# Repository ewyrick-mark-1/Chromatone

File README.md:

# Chromatone

**Author:** Elliot Wyrick

## Overview

Chromatone is an embedded audio visualizer running on the Raspberry Pi RP2350. It samples audio through the ADC, performs a real-time FFT, detects musical notes, and drives an RGB LED output based on the results.

## [Demo video:](https://youtu.be/pOVmz1aZbJg)

## Hardware

- **MCU:** Raspberry Pi RP2350 (overclocked to 300 MHz)
- **Input:** Analog microphone on ADC channel 0 (GPIO 40)
- **Output:** RGB LED via PWM on GPIO 37–39
- **Schematics/PCB:** KiCad project files located in `KiCad/`

## How It Works

Audio is captured at 20 kHz using DMA ping-pong buffers. Each buffer triggers a 16384 point FFT with 50% overlap and a Hanning window applied. Detected frequency peaks are mapped to MIDI notes (A0–C8), and the corresponding hue is output to the RGB LED.

Two display modes are available (toggled via `display_mode` in `main.c`):
- **Mode 0:** Logarithmic frequency spectrum
- **Mode 1:** Musical note detection

## Color Math

Each of the 12 chromatic notes is assigned a fixed hue evenly spaced around the color wheel (360° / 12 = 30° per note), with C at 0° (red) through B at 330° (pink).

Detected peaks are converted to a note index using the standard MIDI formula:

```
n = 12 × log₂(f / 440) + 69
```

When multiple notes are detected simultaneously, their hues are blended using a **circular weighted average**- each hue is converted to a unit vector on the color wheel, weighted by FFT magnitude, and the vectors are summed:

```
x = Σ( cos(hue_i) × weight_i )
y = Σ( sin(hue_i) × weight_i )
blended_hue = atan2(y, x)
```

This handles wraparound correctly (e.g. blending 10° and 350° yields 0°, not 180°).

The blended hue is then smoothed over time using an exponential moving average on the shortest angular path (15% per frame) to avoid jarring color jumps between notes.

Finally, the smoothed hue is converted from HSV (full saturation and brightness) to RGB via the standard piecewise HSV→RGB formula and output as an 8-bit PWM duty cycle on each channel.

## Build & Flash

This project uses [PlatformIO](https://platformio.org/) with the Proton board target.

```
pio run
pio run --target upload
```

Serial monitor at 115200 baud:
```
pio device monitor
```

Alternativly, and what I used during development, the platform IO extension works well. It provides gui upload and monitor buttons.

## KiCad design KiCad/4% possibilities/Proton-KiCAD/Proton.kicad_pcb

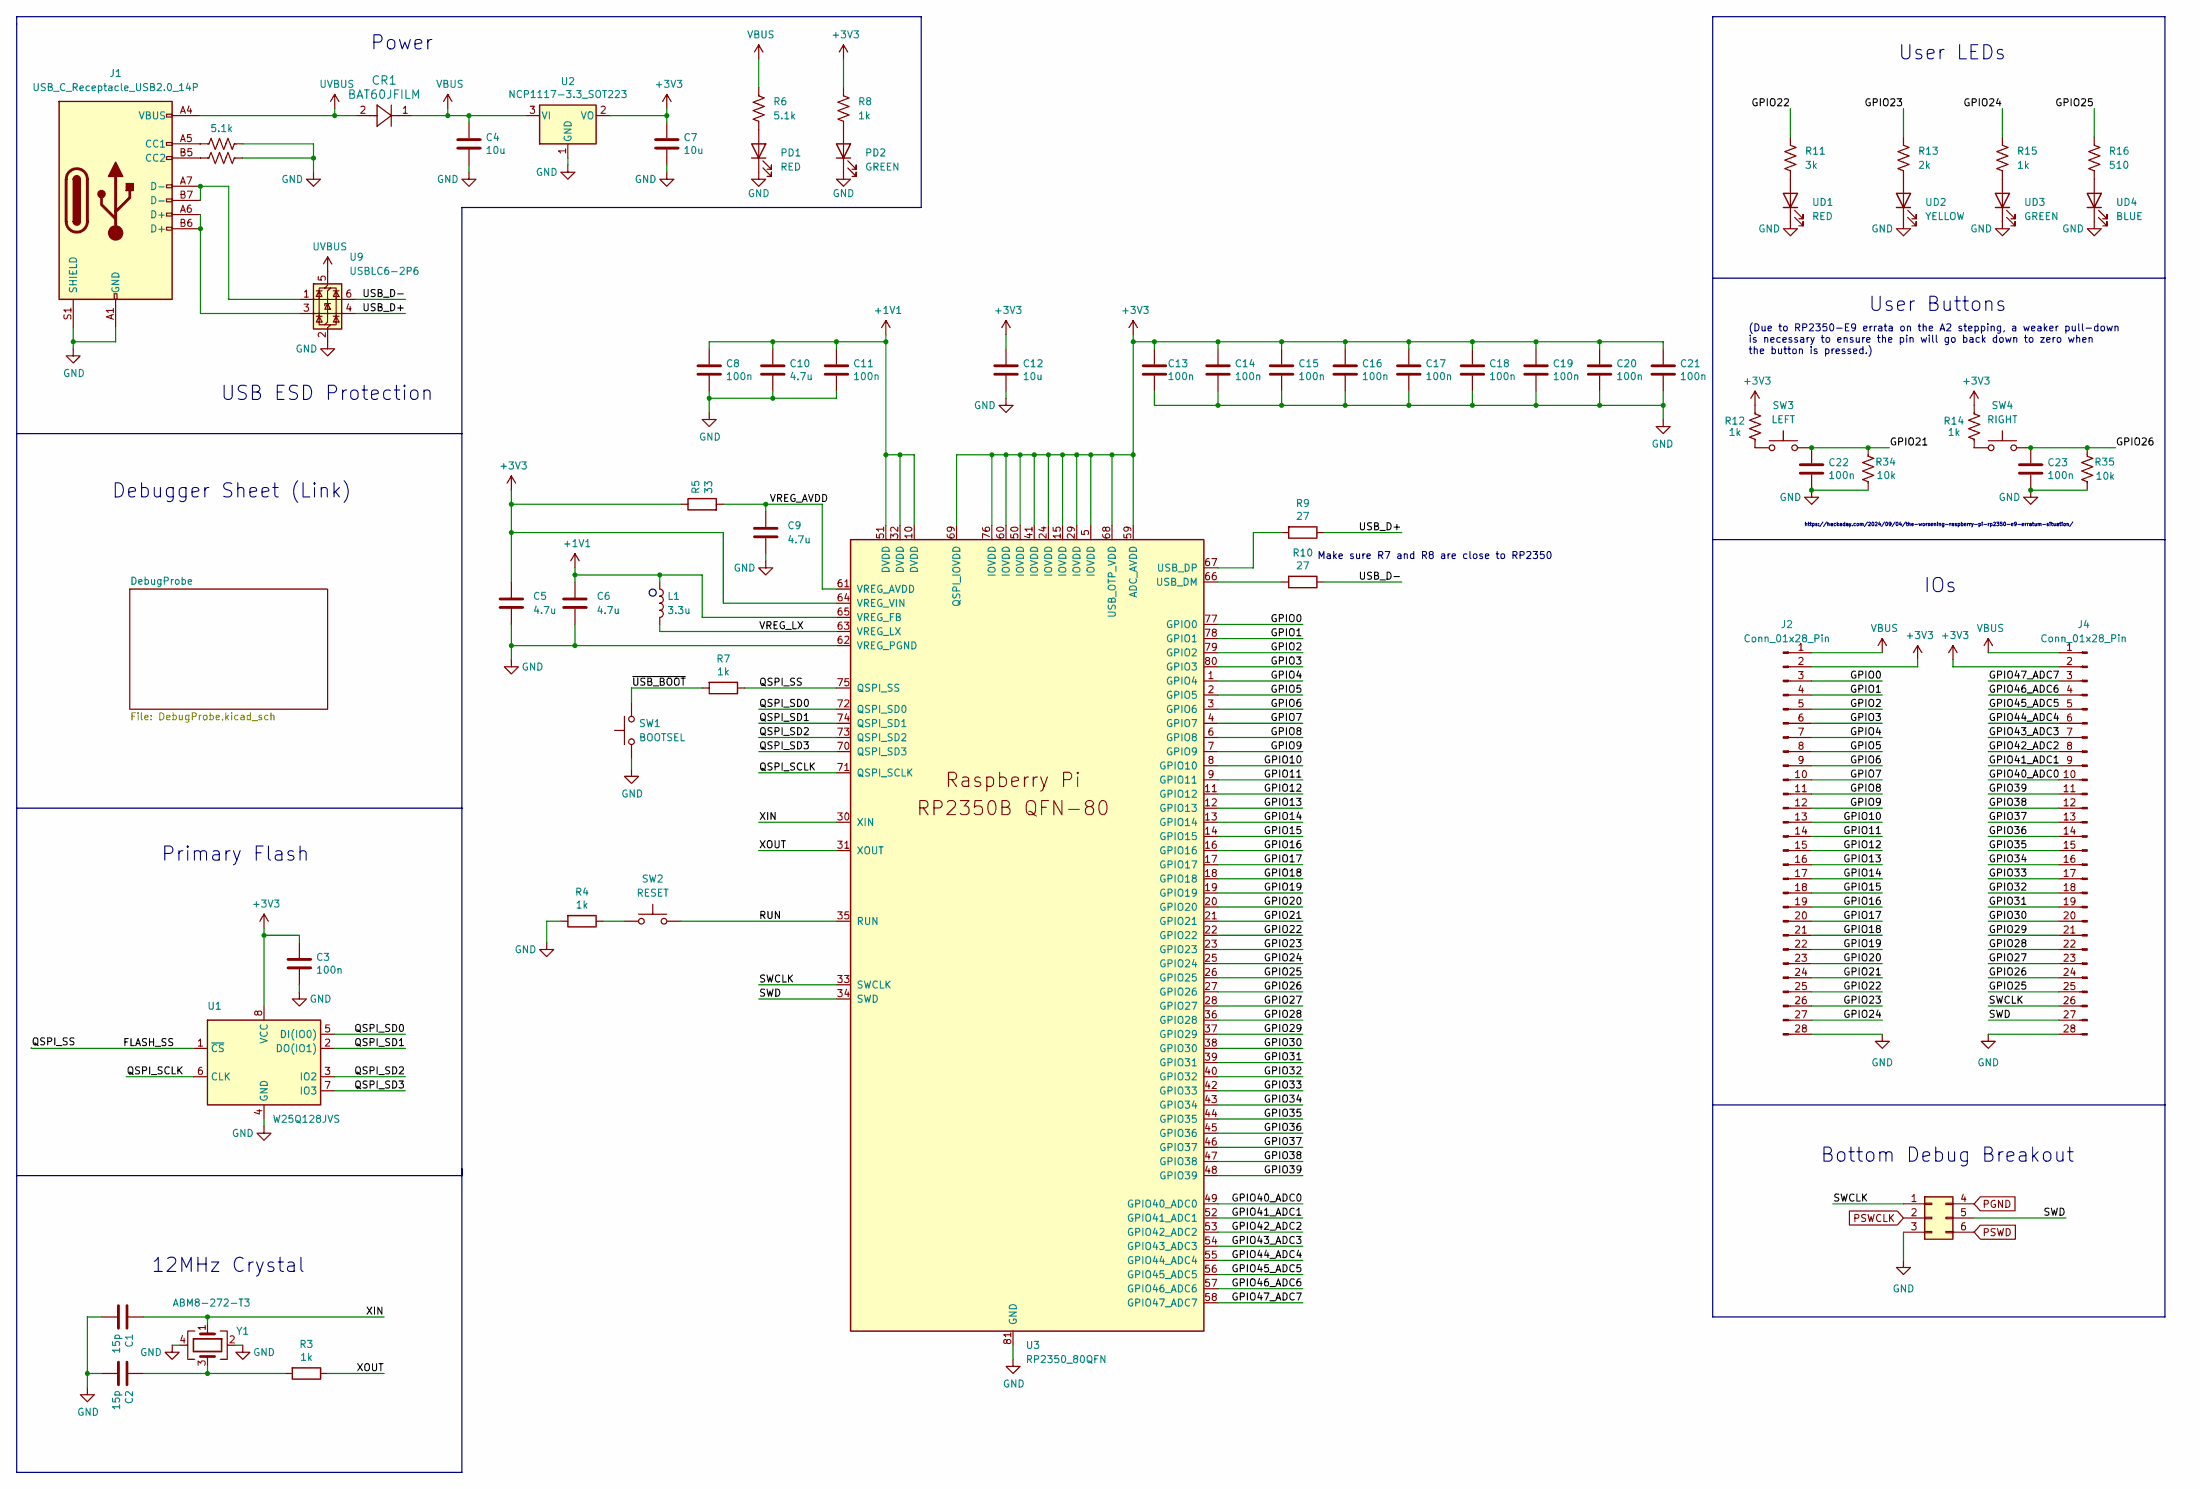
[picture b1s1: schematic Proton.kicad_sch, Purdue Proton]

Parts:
C1, C2: 15p; C_0402_1005Metric
C3, C8, C11, C13, C14, C15, C16, C17, C18, C19, C20, C21, C22, C23: 100n; C_0402_1005Metric
C4, C7, C12: 10u; C_0805_2012Metric
C5, C6: 4.7u; C_0402_1005Metric_small_pads
C9, C10: 4.7u; C_0402_1005Metric
CR1: BAT60JFILM; CR_60JFILM_STM
J1: USB_C_Receptacle_USB2.0_14P; USB_C_Receptacle_G-Switch_GT-USB-7010ASV
J2, J4: Conn_01x28_Pin; PinHeader_1x28_P2.54mm_Vertical
J6: Conn_02x03_Top_Bottom; PinSocket_2x03_P2.54mm_Vertical
L1: 3.3u; L_pol_2016
PD1: RED; LED_0805_2012Metric
PD2: GREEN; LED_0805_2012Metric
R1, R2, R6: 5.1k; R_0402_1005Metric
R3, R4, R7, R8, R12, R14, R15: 1k; R_0402_1005Metric
R5: 33; R_0402_1005Metric
R9, R10: 27; R_0402_1005Metric
R11: 3k; R_0402_1005Metric
R13: 2k; R_0402_1005Metric
R16: 510; R_0402_1005Metric
R34, R35: 10k; R_0402_1005Metric
SW1: BOOTSEL; SW_SPST_PTS647_Sx38
SW2: RESET; SW_SPST_PTS647_Sx38
SW3: LEFT; SW_SPST_PTS647_Sx38
SW4: RIGHT; SW_SPST_PTS647_Sx38
U1: W25Q128JVS; SOIC-8_5.23x5.23mm_P1.27mm
U2: NCP1117-3.3_SOT223; SOT-223-3_TabPin2
U3: RP2350_80QFN; RP2350-QFN-80-1EP_10x10_P0.4mm_EP3.4x3.4mm_ThermalVias
U9: USBLC6-2P6; SOT-666
UD1: RED; LED_0805_2012Metric
UD2: YELLOW; LED_0805_2012Metric
UD3: GREEN; LED_0805_2012Metric
UD4: BLUE; LED_0805_2012Metric
Y1: ABM8-272-T3; Crystal_SMD_3225-4Pin_3.2x2.5mm

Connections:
+1V1: C6.1, C8.1, C10.1, C11.1, L1.1, U3.10 (DVDD), U3.32 (DVDD), U3.51 (DVDD), U3.65 (VREG_FB)
+3V3: C3.1, C5.1, C7.1, C12.1, C13.1, C14.1, C15.1, C16.1, C17.1, C18.1, C19.1, C20.1, C21.1, J2.2, J4.2, R5.1, R8.1, R12.1, R14.1, U1.8 (VCC), U2.2 (VO), U3.5 (IOVDD), U3.15 (IOVDD), U3.24 (IOVDD), U3.29 (IOVDD), U3.41 (IOVDD), U3.50 (IOVDD), U3.59 (ADC_AVDD), U3.60 (IOVDD), U3.64 (VREG_VIN), U3.68 (USB_OTP_VDD), U3.69 (QSPI_IOVDD), U3.76 (IOVDD)
/FLASH_SS: R7.1, U1.1 (~CS), U3.75 (QSPI_SS)
/GPIO0: J2.3, U3.77 (GPIO0)
/GPIO1: J2.4, U3.78 (GPIO1)
/GPIO2: J2.5, U3.79 (GPIO2)
/GPIO3: J2.6, U3.80 (GPIO3)
/GPIO4: J2.7, U3.1 (GPIO4)
/GPIO5: J2.8, U3.2 (GPIO5)
/GPIO6: J2.9, U3.3 (GPIO6)
/GPIO7: J2.10, U3.4 (GPIO7)
/GPIO8: J2.11, U3.6 (GPIO8)
/GPIO9: J2.12, U3.7 (GPIO9)
/GPIO10: J2.13, U3.8 (GPIO10)
/GPIO11: J2.14, U3.9 (GPIO11)
/GPIO12: J2.15, U3.11 (GPIO12)
/GPIO13: J2.16, U3.12 (GPIO13)
/GPIO14: J2.17, U3.13 (GPIO14)
/GPIO15: J2.18, U3.14 (GPIO15)
/GPIO16: J2.19, U3.16 (GPIO16)
/GPIO17: J2.20, U3.17 (GPIO17)
/GPIO18: J2.21, U3.18 (GPIO18)
/GPIO19: J2.22, U3.19 (GPIO19)
/GPIO20: J2.23, U3.20 (GPIO20)
/GPIO21: C22.1, J2.24, R34.2, SW3.2, U3.21 (GPIO21)
/GPIO22: J2.25, R11.1, U3.22 (GPIO22)
/GPIO23: J2.26, R13.1, U3.23 (GPIO23)
/GPIO24: J2.27, R15.1, U3.25 (GPIO24)
/GPIO25: J4.25, R16.1, U3.26 (GPIO25)
/GPIO26: C23.1, J4.24, R35.2, SW4.2, U3.27 (GPIO26)
/GPIO27: J4.23, U3.28 (GPIO27)
/GPIO28: J4.22, U3.36 (GPIO28)
/GPIO29: J4.21, U3.37 (GPIO29)
/GPIO30: J4.20, U3.38 (GPIO30)
/GPIO31: J4.19, U3.39 (GPIO31)
/GPIO32: J4.18, U3.40 (GPIO32)
/GPIO33: J4.17, U3.42 (GPIO33)
/GPIO34: J4.16, U3.43 (GPIO34)
/GPIO35: J4.15, U3.44 (GPIO35)
/GPIO36: J4.14, U3.45 (GPIO36)
/GPIO37: J4.13, U3.46 (GPIO37)
/GPIO38: J4.12, U3.47 (GPIO38)
/GPIO39: J4.11, U3.48 (GPIO39)
/GPIO40_ADC0: J4.10, U3.49 (GPIO40_ADC0)
/GPIO41_ADC1: J4.9, U3.52 (GPIO41_ADC1)
/GPIO42_ADC2: J4.8, U3.53 (GPIO42_ADC2)
/GPIO43_ADC3: J4.7, U3.54 (GPIO43_ADC3)
/GPIO44_ADC4: J4.6, U3.55 (GPIO44_ADC4)
/GPIO45_ADC5: J4.5, U3.56 (GPIO45_ADC5)
/GPIO46_ADC6: J4.4, U3.57 (GPIO46_ADC6)
/GPIO47_ADC7: J4.3, U3.58 (GPIO47_ADC7)
/QSPI_SCLK: U1.6 (CLK), U3.71 (QSPI_SCLK)
/QSPI_SD0: U1.5 (DI(IO0)), U3.72 (QSPI_SD0)
/QSPI_SD1: U1.2 (DO(IO1)), U3.74 (QSPI_SD1)
/QSPI_SD2: U1.3 (IO2), U3.73 (QSPI_SD2)
/QSPI_SD3: U1.7 (IO3), U3.70 (QSPI_SD3)
/RUN: SW2.2, U3.35 (RUN)
/SWCLK: J4.26, J6.1, U3.33 (SWCLK)
/SWD: J4.27, J6.5, U3.34 (SWD)
/USB_D+: R9.1, U9.4 (I/O2)
/USB_D-: R10.1, U9.6 (I/O1)
/VREG_AVDD: C9.1, R5.2, U3.61 (VREG_AVDD)
/VREG_LX: L1.2, U3.63 (VREG_LX)
/XIN: C1.1, U3.30 (XIN), Y1.1
/XOUT: R3.1, U3.31 (XOUT)
/~USB_BOOT: R7.2, SW1.2
GND: C1.2, C2.2, C3.2, C4.2, C5.2, C6.2, C7.2, C8.2, C9.2, C10.2, C11.2, C12.2, C13.2, C14.2, C15.2, C16.2, C17.2, C18.2, C19.2, C20.2, C21.2, C22.2, C23.2, J1.A1 (GND), J1.A12 (GND), J1.B1 (GND), J1.B12 (GND), J1.S1 (SHIELD), J2.28, J4.28, J6.3, PD1.1 (K), PD2.1 (K), R1.2, R2.2, R4.2, R34.1, R35.1, SW1.1, U1.4 (GND), U2.1 (GND), U3.62 (VREG_PGND), U3.81 (GND), U9.2 (GND), UD1.1 (K), UD2.1 (K), UD3.1 (K), UD4.1 (K), Y1.2, Y1.4
unnamed: C2.1, R3.2, Y1.3
unnamed: J1.A5 (CC1), R1.1
unnamed: J1.B5 (CC2), R2.1
unnamed: J1.A6 (D+), J1.B6 (D+), U9.3 (I/O2)
unnamed: J1.A7 (D-), J1.B7 (D-), U9.1 (I/O1)
unnamed: PD1.2 (A), R6.2
unnamed: PD2.2 (A), R8.2
unnamed: R4.1, SW2.1
unnamed: R12.2, SW3.1
unnamed: R14.2, SW4.1
unnamed: R10.2, U3.66 (USB_DM)
unnamed: R9.2, U3.67 (USB_DP)
unnamed: R11.2, UD1.2 (A)
unnamed: R13.2, UD2.2 (A)
unnamed: R15.2, UD3.2 (A)
unnamed: R16.2, UD4.2 (A)
PGND: J6.4; also elsewhere on the board
PSWCLK: J6.2; also elsewhere on the board
PSWD: J6.6; also elsewhere on the board
UVBUS: CR1.2, J1.A4 (VBUS), J1.A9 (VBUS), J1.B4 (VBUS), J1.B9 (VBUS), U9.5 (VBUS)
VBUS: C4.1, CR1.1, J2.1, J4.1, R6.1, U2.3 (VI)

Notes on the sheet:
https://hackaday.com/2024/09/04/the-worsening-raspberry-pi-rp2350-e9-erratum-situation/
IOs
12MHz Crystal
Bottom Debug Breakout
Primary Flash
User LEDs
Make sure R7 and R8 are close to RP2350
Debugger Sheet (Link)
USB ESD Protection
User Buttons
Power
(Due to RP2350-E9 errata on the A2 stepping, a weaker pull-down is necessary to ensure the pin will go back down to zero when the button is pressed.)

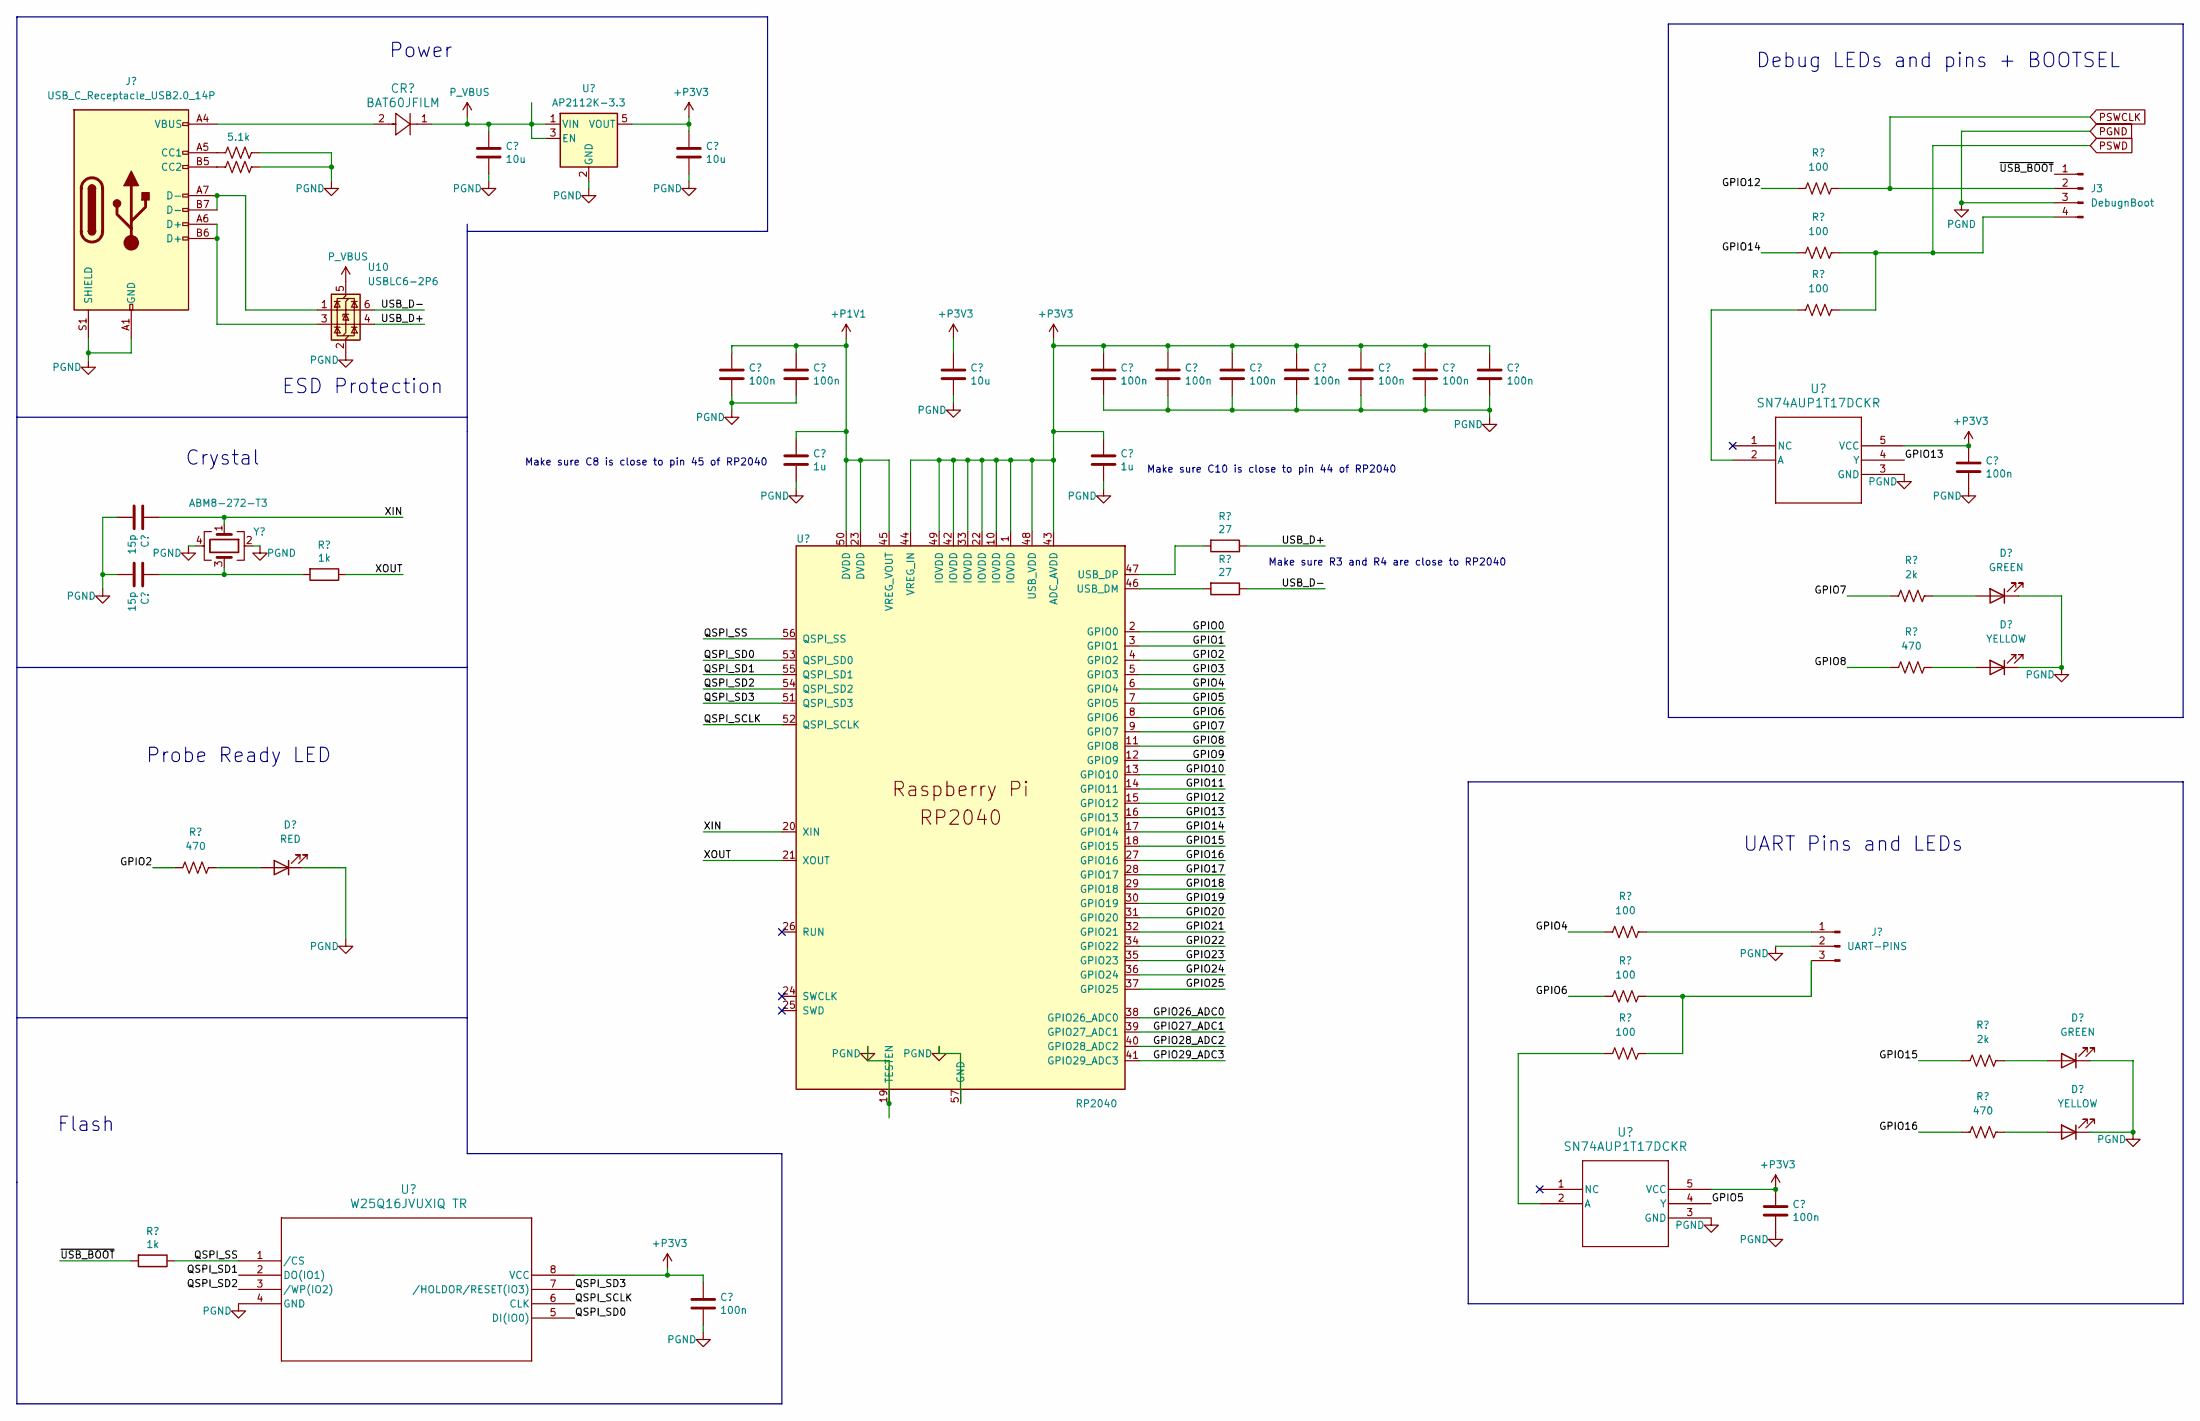
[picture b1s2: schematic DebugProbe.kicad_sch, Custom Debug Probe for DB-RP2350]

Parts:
C24, C25: 15p; C_0402_1005Metric
C26: 10u; C_0805_2012Metric
C27, C32: 10u; C_0603_1608Metric
C28, C29, C30, C33, C35, C36, C37, C38, C39, C40, C41, C42: 100n; C_0402_1005Metric
C31, C34: 1u; C_0402_1005Metric
CR2: BAT60JFILM; CR_60JFILM_STM
D1: RED; D_0402_1005Metric
D2, D4: GREEN; D_0402_1005Metric
D3, D5: YELLOW; D_0402_1005Metric
J3: DebugnBoot; PinHeader_1x04_P2.54mm_Vertical
J5: USB_C_Receptacle_USB2.0_14P; USB_C_Receptacle_G-Switch_GT-USB-7010ASV
J7: UART-PINS; PinHeader_1x03_P2.54mm_Vertical
R17, R20: 1k; R_0402_1005Metric
R18, R19: 5.1k; R_0402_1005Metric
R21, R22: 27; R_0402_1005Metric
R23, R31, R33: 470; R_0402_1005Metric
R24, R25, R26, R27, R28, R29: 100; R_0402_1005Metric
R30, R32: 2k; R_0402_1005Metric
U4: W25Q16JVUXIQ TR; USON-8_UX_2x3x0p6_WIN
U5: AP2112K-3.3; SOT-23-5
U6: RP2040; RP2040-QFN-56
U7, U8: SN74AUP1T17DCKR; DCK5
U10: USBLC6-2P6; SOT-666
Y2: ABM8-272-T3; Crystal_SMD_3225-4Pin_3.2x2.5mm

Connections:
+P1V1: C28.1, C30.1, C31.1, U6.23 (DVDD), U6.45 (VREG_VOUT), U6.50 (DVDD)
+P3V3: C27.1, C29.1, C32.1, C33.1, C34.1, C35.1, C36.1, C37.1, C38.1, C39.1, C40.1, C41.1, C42.1, U4.8 (VCC), U5.5 (VOUT), U6.1 (IOVDD), U6.10 (IOVDD), U6.22 (IOVDD), U6.33 (IOVDD), U6.42 (IOVDD), U6.43 (ADC_AVDD), U6.44 (VREG_IN), U6.48 (USB_VDD), U6.49 (IOVDD), U7.5 (VCC), U8.5 (VCC)
/DebugProbe/GPIO0: U6.2 (GPIO0)
/DebugProbe/GPIO1: U6.3 (GPIO1)
/DebugProbe/GPIO2: R23.1, U6.4 (GPIO2)
/DebugProbe/GPIO3: U6.5 (GPIO3)
/DebugProbe/GPIO4: R24.1, U6.6 (GPIO4)
/DebugProbe/GPIO5: U6.7 (GPIO5), U7.4 (Y)
/DebugProbe/GPIO6: R25.1, U6.8 (GPIO6)
/DebugProbe/GPIO7: R30.1, U6.9 (GPIO7)
/DebugProbe/GPIO8: R31.1, U6.11 (GPIO8)
/DebugProbe/GPIO9: U6.12 (GPIO9)
/DebugProbe/GPIO10: U6.13 (GPIO10)
/DebugProbe/GPIO11: U6.14 (GPIO11)
/DebugProbe/GPIO12: R27.1, U6.15 (GPIO12)
/DebugProbe/GPIO13: U6.16 (GPIO13), U8.4 (Y)
/DebugProbe/GPIO14: R28.1, U6.17 (GPIO14)
/DebugProbe/GPIO15: R32.1, U6.18 (GPIO15)
/DebugProbe/GPIO16: R33.1, U6.27 (GPIO16)
/DebugProbe/GPIO17: U6.28 (GPIO17)
/DebugProbe/GPIO18: U6.29 (GPIO18)
/DebugProbe/GPIO19: U6.30 (GPIO19)
/DebugProbe/GPIO20: U6.31 (GPIO20)
/DebugProbe/GPIO21: U6.32 (GPIO21)
/DebugProbe/GPIO22: U6.34 (GPIO22)
/DebugProbe/GPIO23: U6.35 (GPIO23)
/DebugProbe/GPIO24: U6.36 (GPIO24)
/DebugProbe/GPIO25: U6.37 (GPIO25)
/DebugProbe/GPIO26_ADC0: U6.38 (GPIO26_ADC0)
/DebugProbe/GPIO27_ADC1: U6.39 (GPIO27_ADC1)
/DebugProbe/GPIO28_ADC2: U6.40 (GPIO28_ADC2)
/DebugProbe/GPIO29_ADC3: U6.41 (GPIO29_ADC3)
/DebugProbe/QSPI_SCLK: U4.6 (CLK), U6.52 (QSPI_SCLK)
/DebugProbe/QSPI_SD0: U4.5 (DI(IO0)), U6.53 (QSPI_SD0)
/DebugProbe/QSPI_SD1: U4.2 (DO(IO1)), U6.55 (QSPI_SD1)
/DebugProbe/QSPI_SD2: U4.3 (/WP(IO2)), U6.54 (QSPI_SD2)
/DebugProbe/QSPI_SD3: U4.7 (/HOLDOR/RESET(IO3)), U6.51 (QSPI_SD3)
/DebugProbe/QSPI_SS: R17.1, U4.1 (/CS), U6.56 (QSPI_SS)
/DebugProbe/USB_D+: R21.1, U10.4 (I/O2)
/DebugProbe/USB_D-: R22.1, U10.6 (I/O1)
/DebugProbe/XIN: C24.1, U6.20 (XIN), Y2.1
/DebugProbe/XOUT: R20.1, U6.21 (XOUT)
/DebugProbe/~USB_BOOT: J3.1, R17.2
unnamed: C25.1, R20.2, Y2.3
unnamed: CR2.2, J5.A4 (VBUS), J5.A9 (VBUS), J5.B4 (VBUS), J5.B9 (VBUS)
unnamed: D1.2 (A), R23.2
unnamed: D2.2 (A), R30.2
unnamed: D3.2 (A), R31.2
unnamed: D4.2 (A), R32.2
unnamed: D5.2 (A), R33.2
unnamed: J5.A5 (CC1), R18.1
unnamed: J5.B5 (CC2), R19.1
unnamed: J5.A6 (D+), J5.B6 (D+), U10.3 (I/O2)
unnamed: J5.A7 (D-), J5.B7 (D-), U10.1 (I/O1)
unnamed: J7.1, R24.2
unnamed: J7.3, R25.2, R26.2
unnamed: R22.2, U6.46 (USB_DM)
unnamed: R21.2, U6.47 (USB_DP)
unnamed: R26.1, U7.2 (A)
unnamed: R29.1, U8.2 (A)
PGND: C24.2, C25.2, C26.2, C27.2, C28.2, C29.2, C30.2, C31.2, C32.2, C33.2, C34.2, C35.2, C36.2, C37.2, C38.2, C39.2, C40.2, C41.2, C42.2, D1.1 (K), D2.1 (K), D3.1 (K), D4.1 (K), D5.1 (K), J3.3, J5.A1 (GND), J5.A12 (GND), J5.B1 (GND), J5.B12 (GND), J5.S1 (SHIELD), J7.2, R18.2, R19.2, U4.4 (GND), U5.2 (GND), U6.19 (TESTEN), U6.57 (GND), U7.3 (GND), U8.3 (GND), U10.2 (GND), Y2.2, Y2.4; also elsewhere on the board
PSWCLK: J3.2, R27.2; also elsewhere on the board
PSWD: J3.4, R28.2, R29.2; also elsewhere on the board
P_VBUS: C26.1, CR2.1, U5.1 (VIN), U5.3 (EN), U10.5 (VBUS)

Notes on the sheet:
ESD Protection
Probe Ready LED
Crystal
Power
Make sure C8 is close to pin 45 of RP2040
Make sure C10 is close to pin 44 of RP2040
UART Pins and LEDs
Debug LEDs and pins + BOOTSEL
Make sure R3 and R4 are close to RP2040
Flash

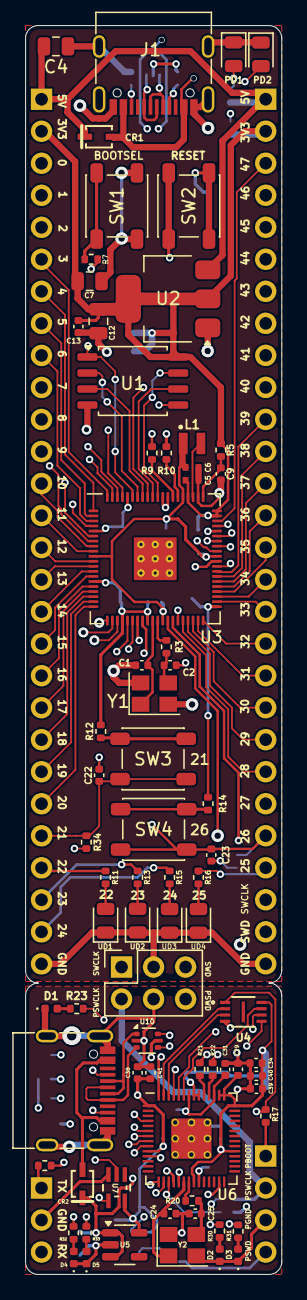
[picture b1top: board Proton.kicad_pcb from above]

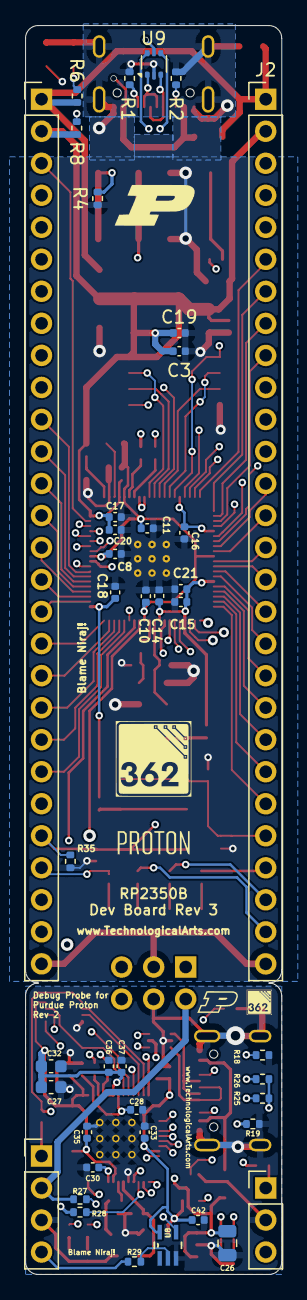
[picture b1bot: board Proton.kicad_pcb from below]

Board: 4 copper layers, 20.3 x 99.1 mm, 114 parts (41 on the bottom side), 130 nets.

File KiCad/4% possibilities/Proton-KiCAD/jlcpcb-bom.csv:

Designator,Footprint,Quantity,Value,LCSC Part #
"C1, C2, C24, C25",402,4,15p,C1548
"C10, C5, C6, C9",402,4,4.7u,C23733
"C11, C13, C14, C15, C16, C17, C18, C19, C20, C21, C22, C23, C28, C29, C3, C30, C33, C35, C36, C37, C38, C39, C40, C41, C42, C8",402,26,100n,C1525
"C12, C26, C4, C7",805,4,10u,C15850
"C27, C32",603,2,10u,C19702
"C31, C34",402,2,1u,C52923
"CR1, CR2",CR_60JFILM_STM,2,BAT60JFILM,C133103
D1,402,1,RED,C397045
"D2, D4",402,2,GREEN,C434446
"D3, D5",402,2,YELLOW,C130721
"J1, J5",USB_C_Receptacle_G-Switch_GT-USB-7010ASV,2,USB_C_Receptacle_USB2.0_14P,C2988369
L1,L_pol_2016,1,3.3u,C42411119
"PD1, UD1",805,2,RED,C2295
"PD2, UD3",805,2,GREEN,C2297
"R1, R18, R19, R2, R6, R8",402,4,5.1k,C25905
"R10, R21, R22, R9",402,4,27,C137890
R11,402,1,3k,C25559
R13,402,1,2k,C4109
R16,402,1,510,C25123
"R12, R14, R15, R17, R20, R3, R4, R7",402,13,1k,C11702
"R34, R35",402,2,10k,C25531
"R23, R31, R33",402,5,470,C25117
"R30, R32",402,2,2k,C4109
"R24, R25, R26, R27, R28, R29",402,6,100,C25076
R5,402,1,33,C25105
SW1,SW_SPST_PTS647_Sx38,1,BOOTSEL,C2689502
SW2,SW_SPST_PTS647_Sx38,1,RESET,C2689502
SW3,SW_SPST_PTS647_Sx38,1,LEFT,C2689502
SW4,SW_SPST_PTS647_Sx38,1,RIGHT,C2689502
U1,SOIC-8_5.23x5.23mm_P1.27mm,1,W25Q128JVS,C97521
"U10, U9",SOT-666,2,USBLC6-2P6,C15999
U2,SOT-223-3_TabPin2,1,NCP1117-3.3_SOT223,C26537
U3,RP2350-QFN-80-1EP_10x10_P0.4mm_EP3.4x3.4mm_ThermalVias,1,RP2350_80QFN,C42415655
U4,USON-8_UX_2x3x0p6_WIN,1,W25Q16JVUXIQ TR,C2843335
U5,SOT-23-5,1,AP2112K-3.3,C23380830
U6,RP2040-QFN-56,1,RP2040,C2040
"U7, U8",DCK5,2,SN74AUP1T17DCKR,C2652100
UD2,805,1,YELLOW,C2296
UD4,805,1,BLUE,C2293
"Y1, Y2",Crystal_SMD_3225-4Pin_3.2x2.5mm,2,ABM8-272-T3,C20625731

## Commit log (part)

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2025-11-07 initial
2025-11-13 FFT set up
2025-11-14 minor refactor
2025-11-14 refactor and confirm it works
2025-11-14 FFT working well 2k -20k
2025-11-16 stuff
2025-11-17 PCB V1
2025-11-18 Filters done
    Bandpass is so zesty bro
2025-11-18 Expand FFT range from 2kHz-20kHz to 20Hz-20kHz using 3 ADC channels
    Implemented a 3-channel ADC/DMA system with different sample rates optimized
    for each frequency range based on Nyquist theorem:
    - Channel 0 (GPIO26): 20-7447 Hz @ 16 kHz sample rate (15.625 Hz resolution)
    - Channel 1 (GPIO27): 7242-14773 Hz @ 32 kHz sample rate (31.25 Hz resolution)
    - Channel 2 (GPIO28): 14573-22000 Hz @ 48 kHz sample rate (46.875 Hz resolution)
    Key improvements:
2025-11-18 LTspice confirm
2025-11-19 test
2025-11-19 Updated filters
2025-11-19 27 - 8kHz single FFT with note detection and overclock
2025-11-21 Revert "27 - 8kHz single FFT with note detection and overclock"
    This reverts commit 01ecf81b79f251795c46a9fa0a58924b9dde3f12.
2025-11-23 pwm led output working
2025-11-23 smooting + weighted hue averaging
    looks much more pretty and a little smoother. ~2 hz
2026-05-24 Fix PWM pin mapping and LED logic
    Correct PWM pin assignments to match physical wiring and update LED drive logic for NMOS gating: swap R/G/B pin defines, initialize PWM outputs LOW (LEDs off), and use non-inverted duty values in set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
2026-05-25 add readme
